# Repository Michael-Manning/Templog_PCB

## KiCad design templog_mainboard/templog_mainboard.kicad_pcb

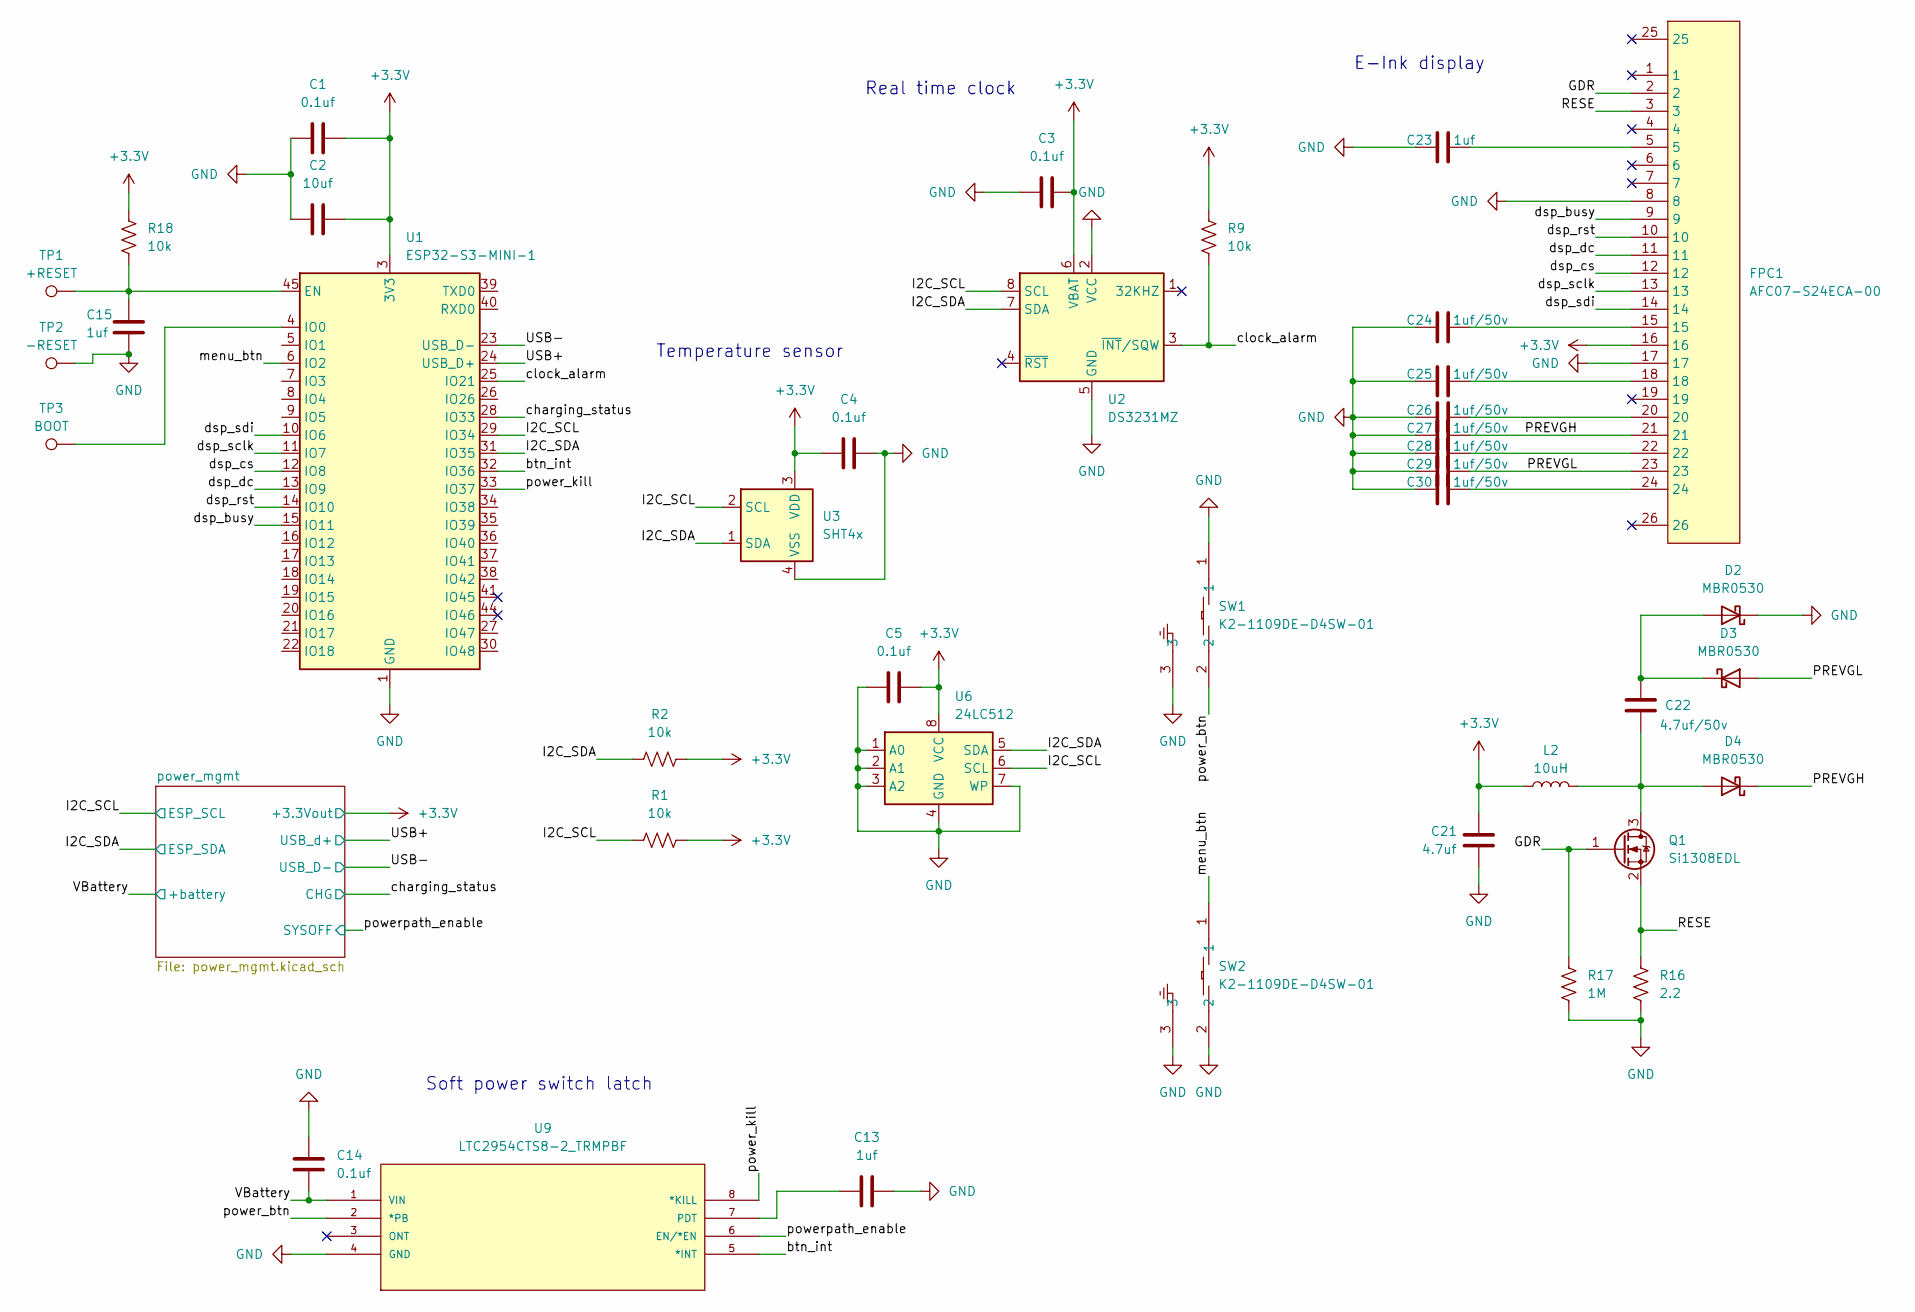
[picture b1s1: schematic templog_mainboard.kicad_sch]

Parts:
C1, C3, C4, C5, C14: 0.1uf; C_0402_1005Metric
C2: 10uf; C_0805_2012Metric
C13, C23: 1uf; C_0603_1608Metric
C15: 1uf; C_0402_1005Metric
C21: 4.7uf; C_0603_1608Metric
C22: 4.7uf/50v; C_0603_1608Metric
C24, C25, C26, C27, C28, C29, C30: 1uf/50v; C_0603_1608Metric
D2, D3, D4: MBR0530; D_SOD-123
FPC1: AFC07-S24ECA-00; FPC-SMD_AFC07-S24ECA-00; LCSC Part C262643
L2: 10uH; L_Sunlord_SWPA4030S
Q1: Si1308EDL; SOT-323_SC-70
R1, R2, R9, R18: 10k; R_0402_1005Metric
R16: 2.2; R_0402_1005Metric
R17: 1M; R_0402_1005Metric
SW1, SW2: K2-1109DE-D4SW-01; KEY-TH_K2-1109DE-CXXW-XX; LCSC Part C223806
TP1: +RESET; TestPoint_Pad_1.0x1.0mm
TP2: -RESET; TestPoint_Pad_1.0x1.0mm
TP3: BOOT; TestPoint_Pad_1.0x1.0mm
U1: ESP32-S3-MINI-1; ESP32-S2-MINI-1
U2: DS3231MZ; SOIC-8_3.9x4.9mm_P1.27mm
U3: SHT4x; Sensirion_DFN-4_1.5x1.5mm_P0.8mm_SHT4x_NoCentralPad
U6: 24LC512; SOIC-8_3.9x4.9mm_P1.27mm
U9: LTC2954CTS8-2_TRMPBF; TSOT-23_TS8; MANUFACTURER_PART_NUMBER ltc2954cts81

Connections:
+3.3V: C1.2, C2.2, C3.2, C4.1, C5.2, C21.1, FPC1.16, L2.1, R1.2, R2.2, R9.1, R18.1, U1.3 (3V3), U2.6 (VBAT), U3.3 (VDD), U6.8 (VCC); also elsewhere on the board
/GDR: FPC1.2, Q1.1 (G), R17.2
/I2C_SCL: R1.1, U1.29 (IO34), U2.8 (SCL), U3.2 (SCL), U6.6 (SCL); also elsewhere on the board
/I2C_SDA: R2.1, U1.31 (IO35), U2.7 (SDA), U3.1 (SDA), U6.5 (SDA); also elsewhere on the board
/PREVGH: C27.2, D4.1 (K), FPC1.21
/PREVGL: C29.2, D3.2 (A), FPC1.23
/RESE: FPC1.3, Q1.2 (S), R16.2
/USB+: U1.24 (USB_D+); also elsewhere on the board
/USB-: U1.23 (USB_D-); also elsewhere on the board
/VBattery: C14.1, U9.1 (VIN); also elsewhere on the board
/btn_int: U1.32 (IO36), U9.5 (*INT)
/charging_status: U1.28 (IO33); also elsewhere on the board
/clock_alarm: R9.2, U1.25 (IO21), U2.3 (~INT/SQW)
/dsp_busy: FPC1.9, U1.15 (IO11)
/dsp_cs: FPC1.12, U1.12 (IO8)
/dsp_dc: FPC1.11, U1.13 (IO9)
/dsp_rst: FPC1.10, U1.14 (IO10)
/dsp_sclk: FPC1.13, U1.11 (IO7)
/dsp_sdi: FPC1.14, U1.10 (IO6)
/menu_btn: SW2.1, U1.6 (IO2)
/power_btn: SW1.2, U9.2 (*PB)
/power_kill: U1.33 (IO37), U9.8 (*KILL)
/powerpath_enable: U9.6 (EN/*EN); also elsewhere on the board
GND: C1.1, C2.1, C3.1, C4.2, C5.1, C13.2, C14.2, C15.2, C21.2, C23.1, C24.1, C25.1, C26.1, C27.1, C28.1, C29.1, C30.1, D2.1 (K), FPC1.8, FPC1.17, R16.1, R17.1, SW1.1, SW1.3, SW2.2, SW2.3, TP2.1, U1.1 (GND), U1.2 (GND), U1.42 (GND), U1.43 (GND), U1.46 (GND), U1.47 (GND), U1.48 (GND), U1.49 (GND), U1.50 (GND), U1.51 (GND), U1.52 (GND), U1.53 (GND), U1.54 (GND), U1.55 (GND), U1.56 (GND), U1.57 (GND), U1.58 (GND), U1.59 (GND), U1.60 (GND), U1.61 (GND), U1.62 (GND), U1.63 (GND), U1.64 (GND), U1.65 (GND), U2.2 (VCC), U2.5 (GND), U3.4 (VSS), U6.1 (A0), U6.2 (A1), U6.3 (A2), U6.4 (GND), U6.7 (WP), U9.4 (GND); also elsewhere on the board
unnamed: C23.2, FPC1.5
unnamed: C24.2, FPC1.15
unnamed: C25.2, FPC1.18
unnamed: C26.2, FPC1.20
unnamed: C28.2, FPC1.22
unnamed: C30.2, FPC1.24
unnamed: C22.1, D2.2 (A), D3.1 (K)
unnamed: C22.2, D4.2 (A), L2.2, Q1.3 (D)
unnamed: C15.1, R18.2, TP1.1, U1.45 (EN)
unnamed: TP3.1, U1.4 (IO0)
unnamed: C13.1, U9.7 (PDT)

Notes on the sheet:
Soft power switch latch
Real time clock
Temperature sensor
E-Ink display

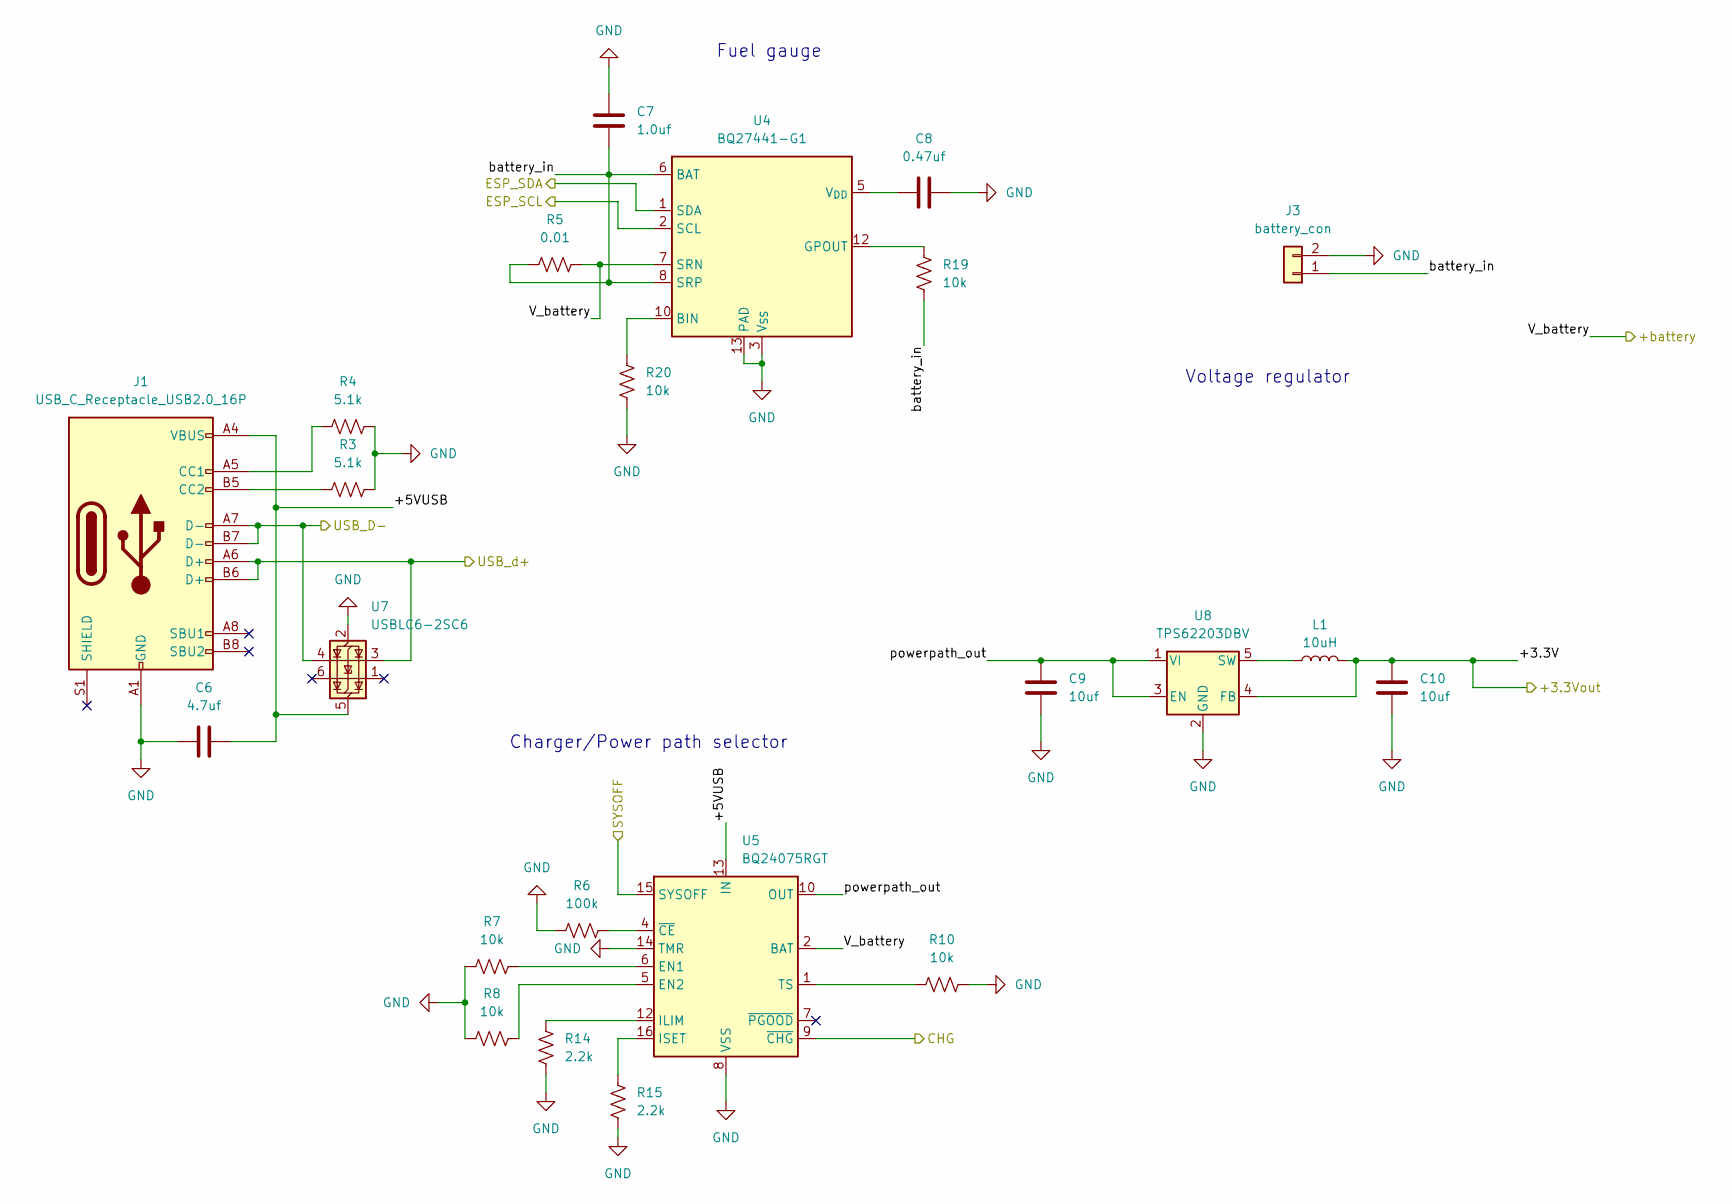
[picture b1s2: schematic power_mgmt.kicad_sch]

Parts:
C6: 4.7uf; C_0603_1608Metric
C7: 1.0uf; C_0402_1005Metric
C8: 0.47uf; C_0402_1005Metric
C9, C10: 10uf; C_0805_2012Metric
J1: USB_C_Receptacle_USB2.0_16P; USB_C_Receptacle_GCT_USB4105-xx-A_16P_TopMnt_Horizontal
J3: battery_con; JST_PH_S2B-PH-K_1x02_P2.00mm_Horizontal
L1: 10uH; L_Sunlord_SWPA4030S
R3, R4: 5.1k; R_0402_1005Metric
R5: 0.01; R_0402_1005Metric
R6: 100k; R_0402_1005Metric
R7, R8, R10, R19, R20: 10k; R_0402_1005Metric
R14, R15: 2.2k; R_0402_1005Metric
U4: BQ27441-G1; Texas_S-PDSO-N12
U5: BQ24075RGT; VQFN-16-1EP_3x3mm_P0.5mm_EP1.6x1.6mm
U7: USBLC6-2SC6; SOT-23-6
U8: TPS62203DBV; SOT-23-5

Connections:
+3.3V: C10.2, L1.2, U8.4 (FB); also elsewhere on the board
/I2C_SCL: U4.2 (SCL); also elsewhere on the board
/I2C_SDA: U4.1 (SDA); also elsewhere on the board
/USB+: J1.A6 (D+), J1.B6 (D+), U7.3 (I/O2); also elsewhere on the board
/USB-: J1.A7 (D-), J1.B7 (D-), U7.4 (I/O2); also elsewhere on the board
/VBattery: R5.2, U4.7 (SRN), U5.2 (BAT), U5.3 (BAT); also elsewhere on the board
/charging_status: U5.9 (~CHG); also elsewhere on the board
/power_mgmt/+5VUSB: C6.1, J1.A4 (VBUS), J1.A9 (VBUS), J1.B4 (VBUS), J1.B9 (VBUS), U5.13 (IN), U7.5 (VBUS)
/power_mgmt/battery_in: C7.2, J3.1, R5.1, R19.1, U4.6 (BAT), U4.8 (SRP)
/power_mgmt/powerpath_out: C9.2, U5.10 (OUT), U5.11 (OUT), U8.1 (VI), U8.3 (EN)
/powerpath_enable: U5.15 (SYSOFF); also elsewhere on the board
GND: C6.2, C7.1, C8.1, C9.1, C10.1, J1.A1 (GND), J1.A12 (GND), J1.B1 (GND), J1.B12 (GND), J3.2, R3.2, R4.2, R6.1, R7.1, R8.1, R10.2, R14.1, R15.1, R20.2, U4.3 (V_{SS}), U4.13 (PAD), U5.8 (VSS), U5.14 (TMR), U5.17 (VSS), U7.2 (GND), U8.2 (GND); also elsewhere on the board
unnamed: J1.A5 (CC1), R4.1
unnamed: J1.B5 (CC2), R3.1
unnamed: R20.1, U4.10 (BIN)
unnamed: R19.2, U4.12 (GPOUT)
unnamed: C8.2, U4.5 (V_{DD})
unnamed: R7.2, U5.6 (EN1)
unnamed: R8.2, U5.5 (EN2)
unnamed: R14.2, U5.12 (ILIM)
unnamed: R15.2, U5.16 (ISET)
unnamed: R10.1, U5.1 (TS)
unnamed: R6.2, U5.4 (~CE)
unnamed: L1.1, U8.5 (SW)

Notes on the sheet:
Voltage regulator
Charger/Power path selector
Fuel gauge

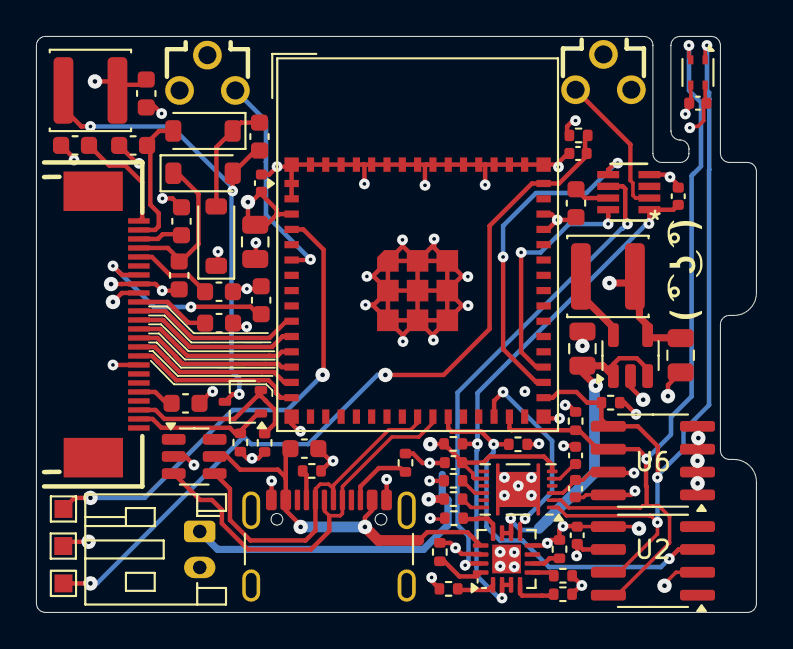
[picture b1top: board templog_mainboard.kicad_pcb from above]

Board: 4 copper layers, 40.0 x 32.0 mm, 63 parts (0 on the bottom side), 50 nets.

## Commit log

2025-05-29 elecricity
2025-06-05 electtrirciy
2025-06-13 time for electricity
2025-06-16 electiricity
2025-06-17 Taseotlkauset
2025-06-18 okay
2025-06-20 asefjikhasefase:
2025-06-27 asejkthas
2025-06-30 laout
2025-07-03 this is an electricity PCB
2025-07-03 ummmmmm uggg uhhh
2025-07-03 electroscity
2025-07-04 :ASEDfasef
2025-07-04 Afsehaselfhasef
2025-07-04 electractiyt
2025-07-05 uuhhuh umm electriciadty
